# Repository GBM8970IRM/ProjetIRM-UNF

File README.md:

# GBM8970 Projet de monitoring de la salle IRM de l'INF

## Context
The following design project aims to develop a real-time measurement and monitoring device for the MRI room of the Unité de Neuroimagerie de Montréal.
This project is carried out as part of the course GBM8970 - Projet intégrateur de Génie biomédical, by a group of five fourth-year students in Biomedical Engineering. The students are Louis-Antoine Delisle, Charlotte Pépin, William Sirois, Emmy Tran-Khanh, and Héloïse Warin, under the supervision of Professor Frédéric Lesage. The final product should centralize various measurements and display them on an interface that contains all the collected information, sending alerts when an abnormal measurement is detected.
Ultimately, this leads to the automation of measuring the inlet and outlet water temperatures of the cooling system of the MRI, its water flow rate, as well as the temperature and humidity of the MRI room. The collected measurements are all sent to a web server, from which they are subsequently displayed on a graphical interface accessible via a web page on computers. 

## Neccessary equipment and parts
The main parts that had to be aquired for this project are the following :
- Arduino Opta for data acquisition and processing
- Arduino Opta expansion (A0602) for reading current from flow meter
- Casing with DIN rails to house the different components
- Fluid thermometer (x2) 
- Humidity and temperature sensor
- Shield for the pre-existing flow meter

## Circuit and PCB design
The PCB was designed using KiCad. The following images show the circuit schematic as well as the design of the PCB :

**!Subject to change/Non official!**

## How to use
Once the device is installed accordingly to the circuit schematic shown above, the aquired data can be accessed via Graffana.
**To be completed.**

## How to follow our work
Since this is a project with several components, an issue is generated for each aspect of the problem to be solved. This ensures that no information is lost by adding comments to a single issue. We invite you to consult these issues to follow the progress of the development of our solution. The list below allows you to easily access the issues corresponding to the key challenges of the project : 

[Temperature and humidity of the MRI room](/../../issues/1)

[Water temperature of the cooling system](/../../issues/2)

[Flow rate of the cooling system](/../../issues/3)

[Data storage](/../../issues/4)

[Monitoring interface](/../../issues/5)

[Alerts](/../../issues/6)

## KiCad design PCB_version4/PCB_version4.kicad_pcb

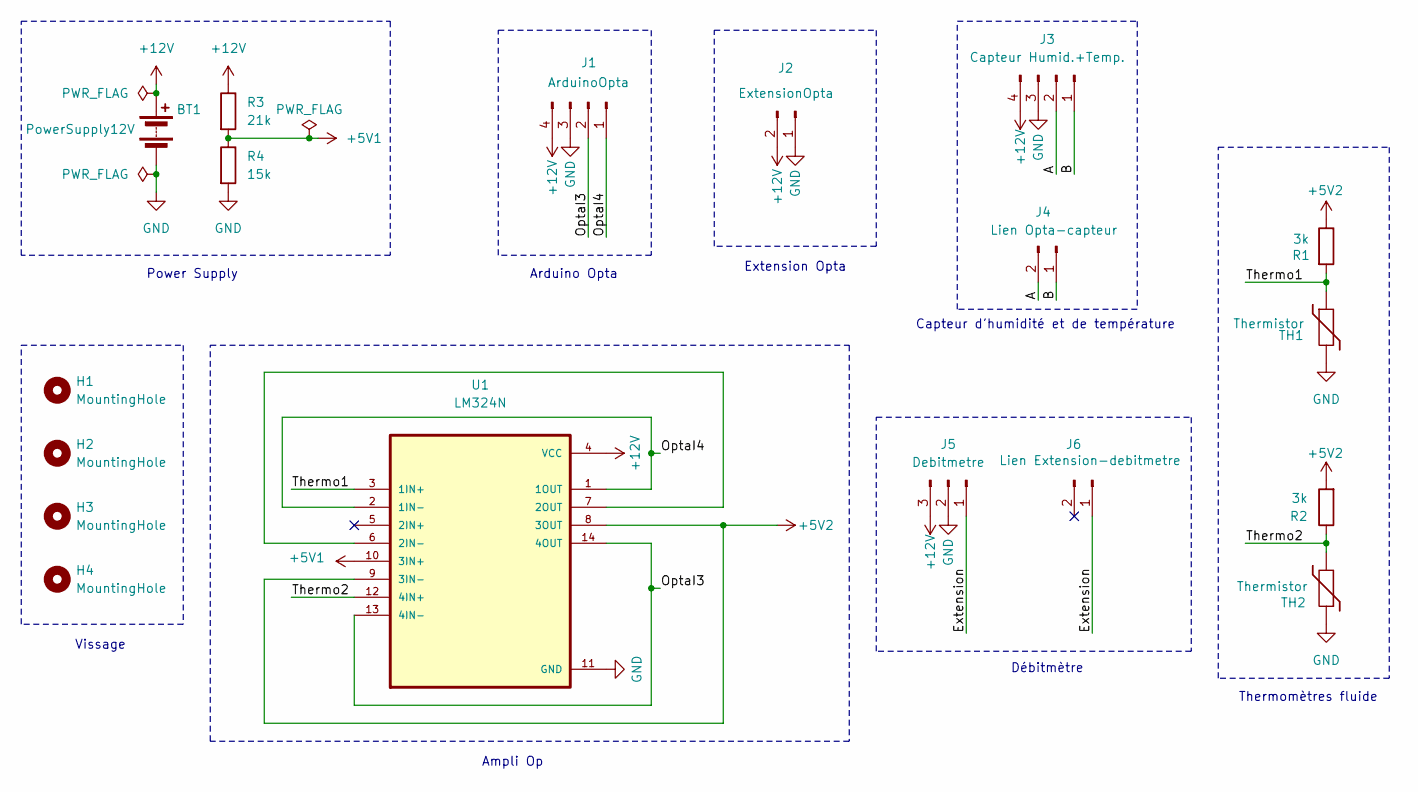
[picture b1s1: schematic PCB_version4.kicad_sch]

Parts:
BT1: PowerSupply12V; JST_EH_S2B-EH_1x02_P2.50mm_Horizontal
H1, H2, H3, H4: MountingHole
J1: ArduinoOpta; JST_EH_S4B-EH_1x04_P2.50mm_Horizontal
J2: ExtensionOpta; JST_EH_S2B-EH_1x02_P2.50mm_Horizontal
J3: Capteur Humid.+Temp.; JST_EH_S4B-EH_1x04_P2.50mm_Horizontal
J4: Lien Opta-capteur; JST_EH_S2B-EH_1x02_P2.50mm_Horizontal
J5: Debitmetre; JST_EH_S3B-EH_1x03_P2.50mm_Horizontal
J6: Lien Extension-debitmetre; JST_EH_S2B-EH_1x02_P2.50mm_Horizontal
R1, R2: 3k; R_Axial_DIN0207_L6.3mm_D2.5mm_P10.16mm_Horizontal
R3: 21k; R_Axial_DIN0207_L6.3mm_D2.5mm_P10.16mm_Horizontal
R4: 15k; R_Axial_DIN0207_L6.3mm_D2.5mm_P10.16mm_Horizontal
TH1, TH2: Thermistor; JST_EH_S2B-EH_1x02_P2.50mm_Horizontal
U1: LM324N; DIP794W45P254L1969H508Q14

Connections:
+5V1: R3.2, R4.1, U1.10 (3IN+)
+5V2: R1.1, R2.2, U1.8 (3OUT), U1.9 (3IN-)
+12V: BT1.1 (+), J1.4, J2.2, J3.4, J5.3, R3.1, U1.4 (VCC)
/A: J3.2, J4.2
/B: J3.1, J4.1
/Extension: J5.1, J6.1
/OptaI3: J1.2, U1.13 (4IN-), U1.14 (4OUT)
/OptaI4: J1.1, U1.1 (1OUT), U1.2 (1IN-)
/Thermo1: R1.2, TH1.1, U1.3 (1IN+)
/Thermo2: R2.1, TH2.2, U1.12 (4IN+)
GND: BT1.2 (-), J1.3, J2.1, J3.3, J5.2, R4.2, TH1.2, TH2.1, U1.11 (GND)
unnamed: U1.6 (2IN-), U1.7 (2OUT)

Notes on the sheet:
Capteur d'humidité et de température
Extension Opta
Thermomètres fluide
Ampli Op
Power Supply
Arduino Opta
Débitmètre
Vissage

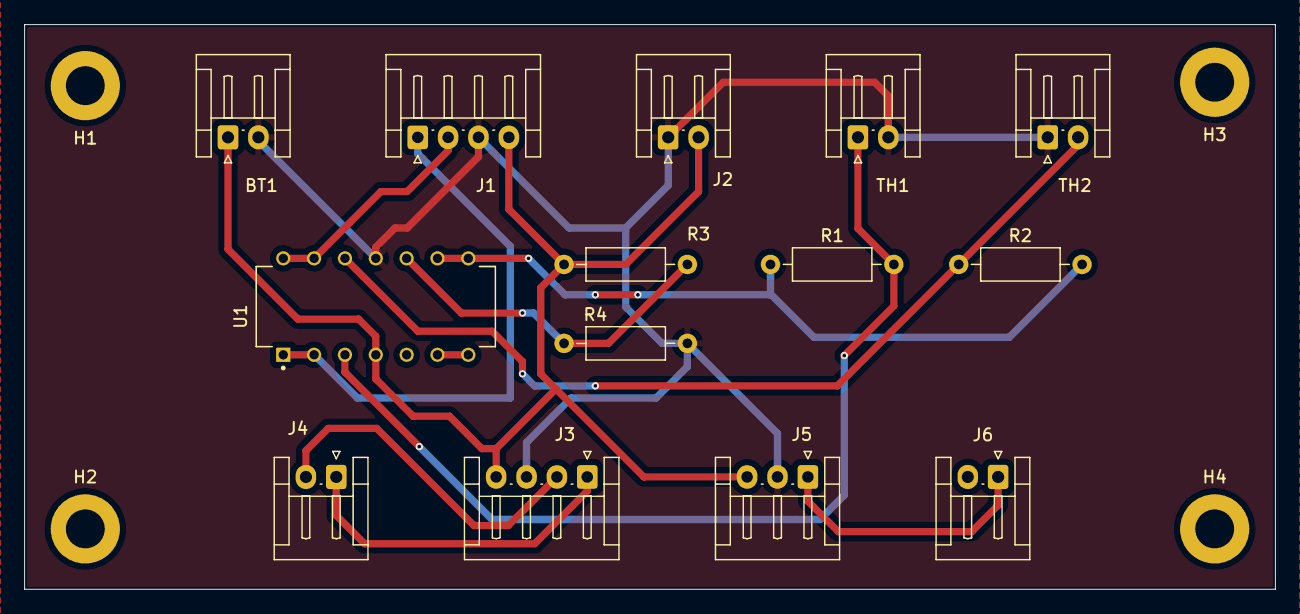
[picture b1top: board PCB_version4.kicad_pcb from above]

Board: 2 copper layers, 103.0 x 46.5 mm, 18 parts (0 on the bottom side), 12 nets.

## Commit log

2024-10-31 Update README.md
    Création de la mise en contexte et de la manière de suivre nos travaux.
2024-10-31 Update README.md
    Correction de faute dans comment suivre nos travaux.
2024-10-31 Update README.md
    Ajout des liens vers les Issues
2024-10-31 Update README.md
    Correction de faute dans les liens
2024-11-05 Test
2024-11-05 Revert "Test"
2024-11-12 Add files via upload
    Transfert de la majorité des documents du googledrive de l'équipe sur le GitHub, incluant les codes arduinos, des schémas des circuits électriques, les documents livrables officiels du cours et les d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
2024-11-13 Ajout communication de données dans les codes
    Les codes ne sont pas fonctionnels encore, il y a une erreur de map au niveau du Arduino Opta lors de la réception des données, et le code du Arduino Nano ne collecte plus de données puisqu'un autre 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
2024-11-14 Ajout codes 13 novembre
    Ajout du code fonctionnel Arduino qui permet l'envoi de données vers le gateway qui sera par la suite scrape par prometheus. Le fichiel yml qui dicte le prometheus est également ajouté. Le gateway fo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
2024-11-16 Add files via upload
    Voici le code qui relie les prises de mesures de température et d'humidité et l'envoie dans pushgateway. Le code n'est pas encore fonctionnel, car il envoie les données arrivent dans pushgateway coll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
2024-11-21 Ajout des codes prototypes fin automne
    Les codes du prototype intermédiaire qui sera présenté au professeur Lesage le 27 novembre.
2024-11-21 Ajout des codes prototypes fin automne
    Code du arduino Nano qui sera part du prototype fonctionnel présenté au professeur Lesage le 27 novembre.
2024-11-25 Fichier json de grafana
    Ajout du fichier de code json qui permet de reproduire l'interface web du dashboard.
2024-11-25 Ajout fichier JSON du grafana
    Ajout du fichier de code json qui permet de reproduire l'interface web du dashboard.
2024-12-06 Create Presentation_04-12-2024
2024-12-06 Update Presentation_04-12-2024
2024-12-06 Presentation_04-12-2024
    Here is Today's presentation converted in Markdown
2024-12-06 Specifications_HTML
2024-12-06 Upload Specifications md
2024-12-06 Upload Design md
2024-12-06 Update CodeArduinoOpta20Nov.ino
    Removed IP address
2024-12-06 Update EnvoiPushgateway-15Nov.ino
    Removed IP address
2025-01-10 Create Meeting_08-01-2025
2025-02-03 Draft_thermometer_S-TH-01
    ArduinoRS485, ArduinoModbus, careful to ID (1, 4097...)
2025-02-03 Rename Opta_29janv.ino to Opta_3fev.ino
2025-02-07 Added modbus reading of MRI room sensor
2025-03-07 Docker compose file to launch applications
2025-03-25 Rename CodeOpta6Fev.ino to CodeOpta.ino
    Change the title to make it final
2025-03-25 Update CodeOpta.ino
    Change to use the httpClient library
2025-03-31 Update CodeOpta.ino
    We added comments and standardized the variable names.
2025-04-01 Update CodeOpta.ino
    Code for the flow meter added.
2025-04-03 Added CADs and Technical Drawing Files
    Is useful for reprinting those components in case they break or become unusable
2025-04-06 Update CodeOpta.ino
    Add the section to convert current to flow
2025-04-07 Update grafana.json
    Update of the json file
2025-04-07 Update prometheus.yml
    change the data to be read each 5 seconds
2025-04-09 Change path
2025-04-09 Changed path
2025-04-09 Rename Measurement_of_Water_Temperature_at_Inlet_and_Outlet_of_the_Chiller_04-12-2024.png to Measurement_of_Water_Temperature_at_Inlet_and_Outlet_of_the_Chiller_04-12-2024.png
2025-04-09 tuned the resistances for better accuracy
2025-04-09 Create Orders and Purchases.md
    list of purchases and orders mae during the project
2025-04-11 UserGuide
2025-04-11 Added images in UserGuide
2025-04-11 Added images in Design doc + modifications
2025-04-11 Added Image in Test doc
